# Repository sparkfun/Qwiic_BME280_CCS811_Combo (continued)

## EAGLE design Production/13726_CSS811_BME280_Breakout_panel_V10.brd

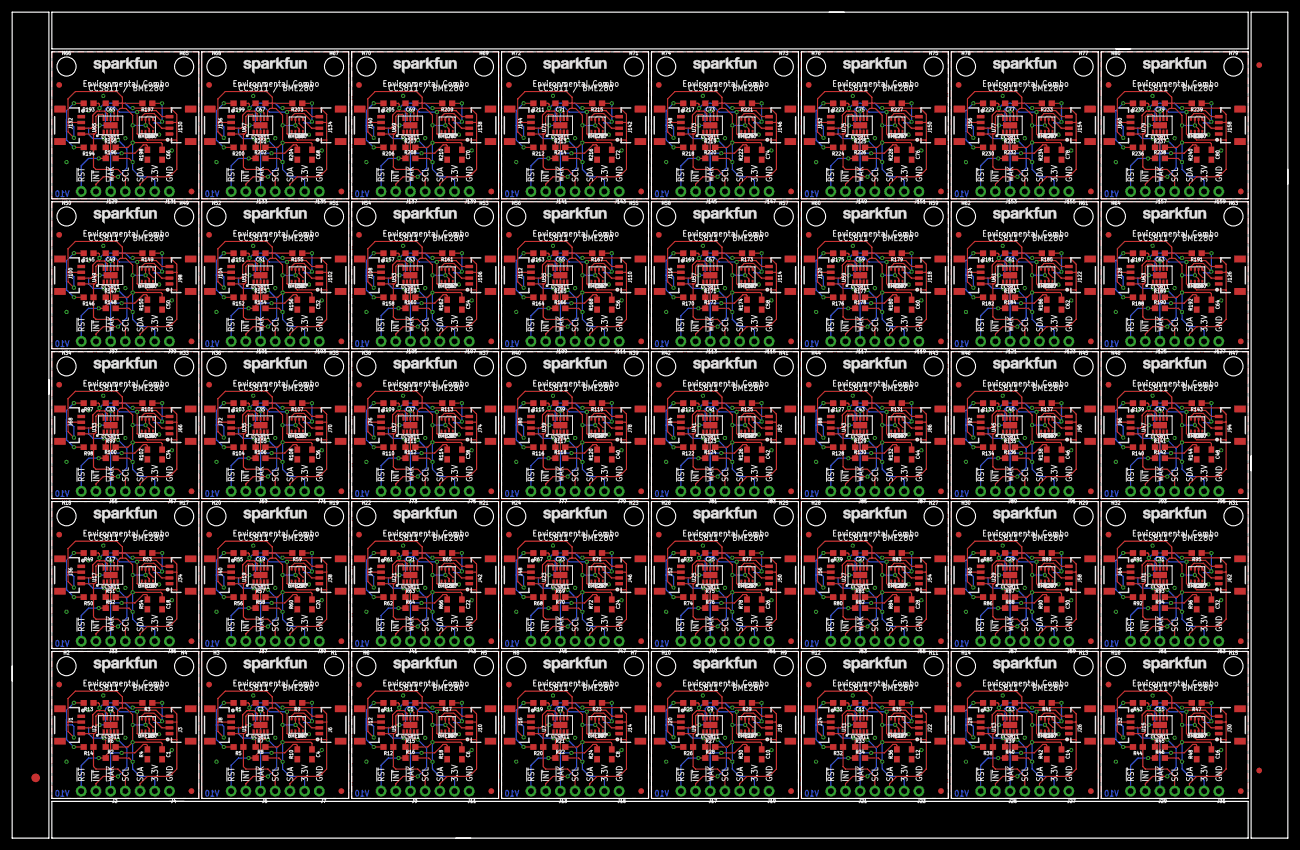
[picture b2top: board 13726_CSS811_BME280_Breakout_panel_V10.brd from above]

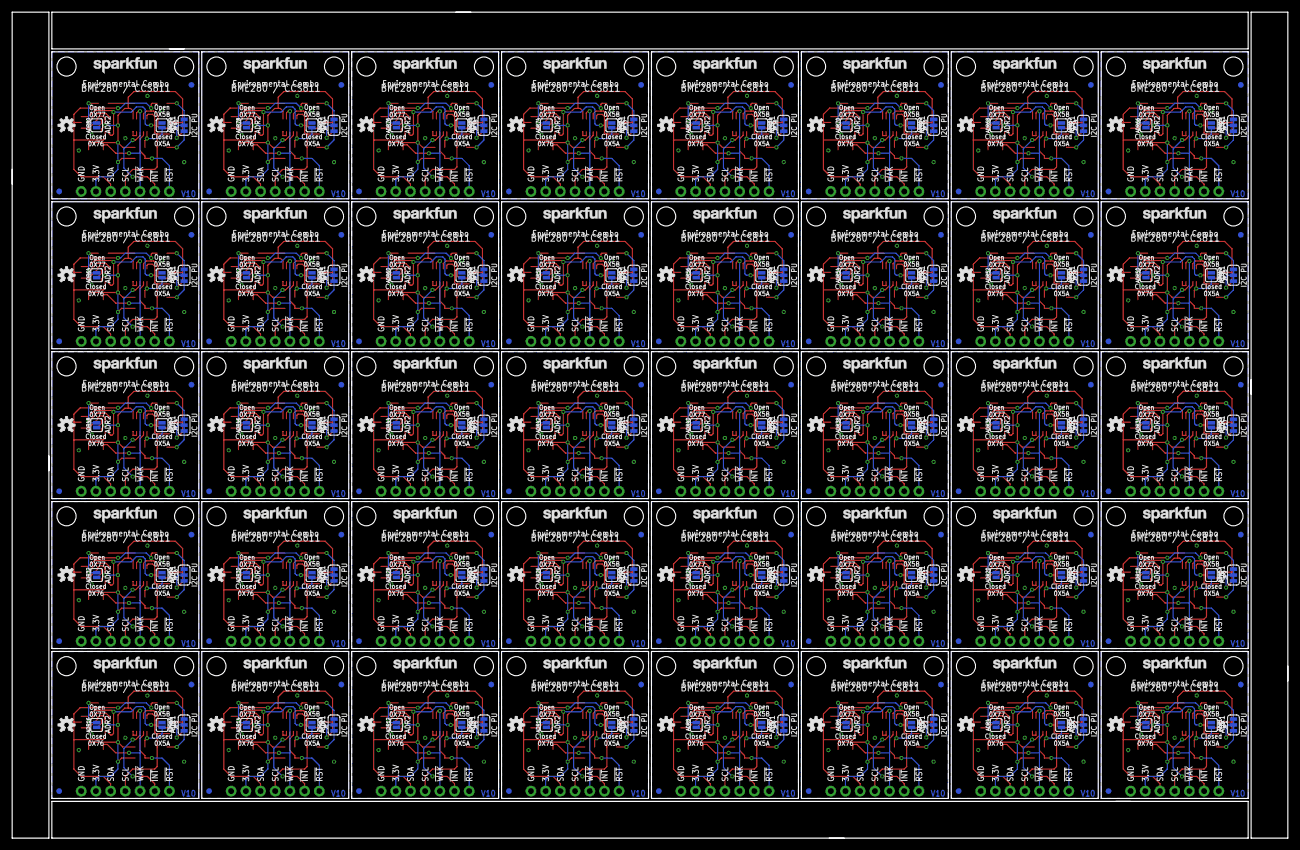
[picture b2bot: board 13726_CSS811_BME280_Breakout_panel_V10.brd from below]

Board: 2 copper layers, 220.5 x 142.7 mm, 1043 parts (280 on the bottom side), 480 nets.

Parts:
ADR1, ADR2, ADR3, ADR4, ADR5, ADR6, ADR7, ADR8, ADR9, ADR10, ADR11, ADR12, ADR13, ADR14, ADR15, ADR16, ADR17, ADR18, ADR19, ADR20, ADR21, ADR22, ADR23, ADR24, ADR25, ADR26, ADR27, ADR28, ADR29, ADR30, ADR31, ADR32, ADR33, ADR34, ADR35, ADR36, ADR37, ADR38, ADR39, ADR40, ADR41, ADR42, ADR43, ADR44, ADR45, ADR46, ADR47, ADR48, ADR49, ADR50, ADR51, ADR52, ADR53, ADR54, ADR55, ADR56, ADR57, ADR58, ADR59, ADR60, ADR61, ADR62, ADR63, ADR64, ADR65, ADR66, ADR67, ADR68, ADR69, ADR70, ADR71, ADR72, ADR73, ADR74, ADR75, ADR76, ADR77, ADR78, ADR79, ADR80: SMT-JUMPER_2_NO_SILK
C1, C4, C6, C8, C10, C12, C14, C16, C18, C20, C22, C24, C26, C28, C30, C32, C34, C36, C38, C40, C42, C44, C46, C48, C50, C52, C54, C56, C58, C60, C62, C64, C66, C68, C70, C72, C74, C76, C78, C80: 0.1uF; 0603
C2, C3, C5, C7, C9, C11, C13, C15, C17, C19, C21, C23, C25, C27, C29, C31, C33, C35, C37, C39, C41, C43, C45, C47, C49, C51, C53, C55, C57, C59, C61, C63, C65, C67, C69, C71, C73, C75, C77, C79: 1.0uF; 0603
E$1: FIDUCIAL-1.5X3
E$7, E$8: FIDUCIAL-1X2
FD1, FD2, FD3, FD4, FD5, FD6, FD7, FD8, FD9, FD10, FD11, FD12, FD13, FD14, FD15, FD16, FD17, FD18, FD19, FD20, FD21, FD22, FD23, FD24, FD25, FD26, FD27, FD28, FD29, FD30, FD31, FD32, FD33, FD34, FD35, FD36, FD37, FD38, FD39, FD40, FD41, FD42, FD43, FD44, FD45, FD46, FD47, FD48, FD49, FD50, FD51, FD52, FD53, FD54, FD55, FD56, FD57, FD58, FD59, FD60, FD61, FD62, FD63, FD64, FD65, FD66, FD67, FD68, FD69, FD70, FD71, FD72, FD73, FD74, FD75, FD76, FD77, FD78, FD79, FD80, FD81, FD82, FD83, FD84, FD85, FD86, FD87, FD88, FD89, FD90, FD91, FD92, FD93, FD94, FD95, FD96, FD97, FD98, FD99, FD100, FD101, FD102, FD103, FD104, FD105, FD106, FD107, FD108, FD109, FD110, FD111, FD112, FD113, FD114, FD115, FD116, FD117, FD118, FD119, FD120, FD121, FD122, FD123, FD124, FD125, FD126, FD127, FD128, FD129, FD130, FD131, FD132, FD133, FD134, FD135, FD136, FD137, FD138, FD139, FD140, FD141, FD142, FD143, FD144, FD145, FD146, FD147, FD148, FD149, FD150, FD151, FD152, FD153, FD154, FD155, FD156, FD157, FD158, FD159, FD160: FIDUCIAL1X2; FIDUCIAL-1X2
H1, H2, H3, H4, H5, H6, H7, H8, H9, H10, H11, H12, H13, H14, H15, H16, H17, H18, H19, H20, H21, H22, H23, H24, H25, H26, H27, H28, H29, H30, H31, H32, H33, H34, H35, H36, H37, H38, H39, H40, H41, H42, H43, H44, H45, H46, H47, H48, H49, H50, H51, H52, H53, H54, H55, H56, H57, H58, H59, H60, H61, H62, H63, H64, H65, H66, H67, H68, H69, H70, H71, H72, H73, H74, H75, H76, H77, H78, H79, H80: STAND-OFF
J1, J3, J6, J8, J10, J12, J14, J16, J18, J20, J22, J24, J26, J28, J30, J32, J34, J36, J38, J40, J42, J44, J46, J48, J50, J52, J54, J56, J58, J60, J62, J64, J66, J68, J70, J72, J74, J76, J78, J80, J82, J84, J86, J88, J90, J92, J94, J96, J98, J100, J102, J104, J106, J108, J110, J112, J114, J116, J118, J120, J122, J124, J126, J128, J130, J132, J134, J136, J138, J140, J142, J144, J146, J148, J150, J152, J154, J156, J158, J160: Qwiic Right Angle; 1X04_1MM_RA
J2, J5, J9, J13, J17, J21, J25, J29, J33, J37, J41, J45, J49, J53, J57, J61, J65, J69, J73, J77, J81, J85, J89, J93, J97, J101, J105, J109, J113, J117, J121, J125, J129, J133, J137, J141, J145, J149, J153, J157: CCS811 Options; 1X03_NO_SILK
J4, J7, J11, J15, J19, J23, J27, J31, J35, J39, J43, J47, J51, J55, J59, J63, J67, J71, J75, J79, J83, J87, J91, J95, J99, J103, J107, J111, J115, J119, J123, J127, J131, J135, J139, J143, J147, J151, J155, J159: PTH; 1X04_NO_SILK
JP1, JP2, JP3, JP4, JP5, JP6, JP7, JP8, JP9, JP10, JP11, JP12, JP13, JP14, JP15, JP16, JP17, JP18, JP19, JP20, JP21, JP22, JP23, JP24, JP25, JP26, JP27, JP28, JP29, JP30, JP31, JP32, JP33, JP34, JP35, JP36, JP37, JP38, JP39, JP40: SMT-JUMPER_3_2-NC_TRACE_SILK
LOGO1, LOGO3, LOGO5, LOGO6, LOGO8, LOGO9, LOGO11, LOGO12, LOGO14, LOGO15, LOGO17, LOGO18, LOGO20, LOGO21, LOGO23, LOGO24, LOGO26, LOGO27, LOGO29, LOGO30, LOGO32, LOGO33, LOGO35, LOGO36, LOGO38, LOGO39, LOGO41, LOGO42, LOGO44, LOGO45, LOGO47, LOGO48, LOGO50, LOGO51, LOGO53, LOGO54, LOGO56, LOGO57, LOGO59, LOGO60, LOGO62, LOGO63, LOGO65, LOGO66, LOGO68, LOGO69, LOGO71, LOGO72, LOGO74, LOGO75, LOGO77, LOGO78, LOGO80, LOGO81, LOGO83, LOGO84, LOGO86, LOGO87, LOGO89, LOGO90, LOGO92, LOGO93, LOGO95, LOGO96, LOGO98, LOGO99, LOGO101, LOGO102, LOGO104, LOGO105, LOGO107, LOGO108, LOGO110, LOGO111, LOGO113, LOGO114, LOGO116, LOGO117, LOGO119, LOGO120: SFE_LOGO_NAME.1_INCH; SFE_LOGO_NAME_.1
LOGO2, LOGO4, LOGO7, LOGO10, LOGO13, LOGO16, LOGO19, LOGO22, LOGO25, LOGO28, LOGO31, LOGO34, LOGO37, LOGO40, LOGO43, LOGO46, LOGO49, LOGO52, LOGO55, LOGO58, LOGO61, LOGO64, LOGO67, LOGO70, LOGO73, LOGO76, LOGO79, LOGO82, LOGO85, LOGO88, LOGO91, LOGO94, LOGO97, LOGO100, LOGO103, LOGO106, LOGO109, LOGO112, LOGO115, LOGO118: OSHW-LOGOS; OSHW-LOGO-S
R1, R2, R5, R8, R11, R12, R13, R14, R16, R19, R20, R22, R25, R26, R28, R31, R32, R34, R37, R38, R40, R43, R44, R46, R49, R50, R52, R55, R56, R58, R61, R62, R64, R67, R68, R70, R73, R74, R76, R79, R80, R82, R85, R86, R88, R91, R92, R94, R97, R98, R100, R103, R104, R106, R109, R110, R112, R115, R116, R118, R121, R122, R124, R127, R128, R130, R133, R134, R136, R139, R140, R142, R145, R146, R148, R151, R152, R154, R157, R158, R160, R163, R164, R166, R169, R170, R172, R175, R176, R178, R181, R182, R184, R187, R188, R190, R193, R194, R196, R199, R200, R202, R205, R206, R208, R211, R212, R214, R217, R218, R220, R223, R224, R226, R229, R230, R232, R235, R236, R238: 4.7k; 0603
R3, R4, R6, R7, R9, R10, R15, R17, R18, R21, R23, R24, R27, R29, R30, R33, R35, R36, R39, R41, R42, R45, R47, R48, R51, R53, R54, R57, R59, R60, R63, R65, R66, R69, R71, R72, R75, R77, R78, R81, R83, R84, R87, R89, R90, R93, R95, R96, R99, R101, R102, R105, R107, R108, R111, R113, R114, R117, R119, R120, R123, R125, R126, R129, R131, R132, R135, R137, R138, R141, R143, R144, R147, R149, R150, R153, R155, R156, R159, R161, R162, R165, R167, R168, R171, R173, R174, R177, R179, R180, R183, R185, R186, R189, R191, R192, R195, R197, R198, R201, R203, R204, R207, R209, R210, R213, R215, R216, R219, R221, R222, R225, R227, R228, R231, R233, R234, R237, R239, R240: 100k; 0603
U1, U2, U5, U7, U9, U11, U13, U15, U17, U19, U21, U23, U25, U27, U29, U31, U33, U35, U37, U39, U41, U43, U45, U47, U49, U51, U53, U55, U57, U59, U61, U63, U65, U67, U69, U71, U73, U75, U77, U79: CCS811; LGA10
U3, U4, U6, U8, U10, U12, U14, U16, U18, U20, U22, U24, U26, U28, U30, U32, U34, U36, U38, U40, U42, U44, U46, U48, U50, U52, U54, U56, U58, U60, U62, U64, U66, U68, U70, U72, U74, U76, U78, U80: BME280; LGA-8-2.5X2.5

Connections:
3.3V: C1.1, C2.1, J1.2, J3.2, J4.2, JP1.2, R2.2, R3.2, R6.2, U2.6, U3.2, U3.6, U3.8
3.3V1: C3.1, C4.1, J6.2, J7.2, J8.2, JP2.2, R7.2, R8.2, R9.2, U1.6, U4.2, U4.6, U4.8
3.3V2: C5.1, C6.1, J10.2, J11.2, J12.2, JP3.2, R15.2, R16.2, R17.2, U5.6, U6.2, U6.6, U6.8
3.3V3: C7.1, C8.1, J14.2, J15.2, J16.2, JP4.2, R21.2, R22.2, R23.2, U7.6, U8.2, U8.6, U8.8
3.3V4: C9.1, C10.1, J18.2, J19.2, J20.2, JP5.2, R27.2, R28.2, R29.2, U9.6, U10.2, U10.6, U10.8
3.3V5: C11.1, C12.1, J22.2, J23.2, J24.2, JP6.2, R33.2, R34.2, R35.2, U11.6, U12.2, U12.6, U12.8
3.3V6: C13.1, C14.1, J26.2, J27.2, J28.2, JP7.2, R39.2, R40.2, R41.2, U13.6, U14.2, U14.6, U14.8
3.3V7: C15.1, C16.1, J30.2, J31.2, J32.2, JP8.2, R45.2, R46.2, R47.2, U15.6, U16.2, U16.6, U16.8
3.3V8: C17.1, C18.1, J34.2, J35.2, J36.2, JP9.2, R51.2, R52.2, R53.2, U17.6, U18.2, U18.6, U18.8
3.3V9: C19.1, C20.1, J38.2, J39.2, J40.2, JP10.2, R57.2, R58.2, R59.2, U19.6, U20.2, U20.6, U20.8
3.3V10: C21.1, C22.1, J42.2, J43.2, J44.2, JP11.2, R63.2, R64.2, R65.2, U21.6, U22.2, U22.6, U22.8
3.3V11: C23.1, C24.1, J46.2, J47.2, J48.2, JP12.2, R69.2, R70.2, R71.2, U23.6, U24.2, U24.6, U24.8
3.3V12: C25.1, C26.1, J50.2, J51.2, J52.2, JP13.2, R75.2, R76.2, R77.2, U25.6, U26.2, U26.6, U26.8
3.3V13: C27.1, C28.1, J54.2, J55.2, J56.2, JP14.2, R81.2, R82.2, R83.2, U27.6, U28.2, U28.6, U28.8
3.3V14: C29.1, C30.1, J58.2, J59.2, J60.2, JP15.2, R87.2, R88.2, R89.2, U29.6, U30.2, U30.6, U30.8
3.3V15: C31.1, C32.1, J62.2, J63.2, J64.2, JP16.2, R93.2, R94.2, R95.2, U31.6, U32.2, U32.6, U32.8
3.3V16: C33.1, C34.1, J66.2, J67.2, J68.2, JP17.2, R99.2, R100.2, R101.2, U33.6, U34.2, U34.6, U34.8
3.3V17: C35.1, C36.1, J70.2, J71.2, J72.2, JP18.2, R105.2, R106.2, R107.2, U35.6, U36.2, U36.6, U36.8
3.3V18: C37.1, C38.1, J74.2, J75.2, J76.2, JP19.2, R111.2, R112.2, R113.2, U37.6, U38.2, U38.6, U38.8
3.3V19: C39.1, C40.1, J78.2, J79.2, J80.2, JP20.2, R117.2, R118.2, R119.2, U39.6, U40.2, U40.6, U40.8
3.3V20: C41.1, C42.1, J82.2, J83.2, J84.2, JP21.2, R123.2, R124.2, R125.2, U41.6, U42.2, U42.6, U42.8
3.3V21: C43.1, C44.1, J86.2, J87.2, J88.2, JP22.2, R129.2, R130.2, R131.2, U43.6, U44.2, U44.6, U44.8
3.3V22: C45.1, C46.1, J90.2, J91.2, J92.2, JP23.2, R135.2, R136.2, R137.2, U45.6, U46.2, U46.6, U46.8
3.3V23: C47.1, C48.1, J94.2, J95.2, J96.2, JP24.2, R141.2, R142.2, R143.2, U47.6, U48.2, U48.6, U48.8
3.3V24: C49.1, C50.1, J98.2, J99.2, J100.2, JP25.2, R147.2, R148.2, R149.2, U49.6, U50.2, U50.6, U50.8
3.3V25: C51.1, C52.1, J102.2, J103.2, J104.2, JP26.2, R153.2, R154.2, R155.2, U51.6, U52.2, U52.6, U52.8
3.3V26: C53.1, C54.1, J106.2, J107.2, J108.2, JP27.2, R159.2, R160.2, R161.2, U53.6, U54.2, U54.6, U54.8
3.3V27: C55.1, C56.1, J110.2, J111.2, J112.2, JP28.2, R165.2, R166.2, R167.2, U55.6, U56.2, U56.6, U56.8
3.3V28: C57.1, C58.1, J114.2, J115.2, J116.2, JP29.2, R171.2, R172.2, R173.2, U57.6, U58.2, U58.6, U58.8
3.3V29: C59.1, C60.1, J118.2, J119.2, J120.2, JP30.2, R177.2, R178.2, R179.2, U59.6, U60.2, U60.6, U60.8
3.3V30: C61.1, C62.1, J122.2, J123.2, J124.2, JP31.2, R183.2, R184.2, R185.2, U61.6, U62.2, U62.6, U62.8
3.3V31: C63.1, C64.1, J126.2, J127.2, J128.2, JP32.2, R189.2, R190.2, R191.2, U63.6, U64.2, U64.6, U64.8
3.3V32: C65.1, C66.1, J130.2, J131.2, J132.2, JP33.2, R195.2, R196.2, R197.2, U65.6, U66.2, U66.6, U66.8
3.3V33: C67.1, C68.1, J134.2, J135.2, J136.2, JP34.2, R201.2, R202.2, R203.2, U67.6, U68.2, U68.6, U68.8
3.3V34: C69.1, C70.1, J138.2, J139.2, J140.2, JP35.2, R207.2, R208.2, R209.2, U69.6, U70.2, U70.6, U70.8
3.3V35: C71.1, C72.1, J142.2, J143.2, J144.2, JP36.2, R213.2, R214.2, R215.2, U71.6, U72.2, U72.6, U72.8
3.3V36: C73.1, C74.1, J146.2, J147.2, J148.2, JP37.2, R219.2, R220.2, R221.2, U73.6, U74.2, U74.6, U74.8
3.3V37: C75.1, C76.1, J150.2, J151.2, J152.2, JP38.2, R225.2, R226.2, R227.2, U75.6, U76.2, U76.6, U76.8
3.3V38: C77.1, C78.1, J154.2, J155.2, J156.2, JP39.2, R231.2, R232.2, R233.2, U77.6, U78.2, U78.6, U78.8
3.3V39: C79.1, C80.1, J158.2, J159.2, J160.2, JP40.2, R237.2, R238.2, R239.2, U79.6, U80.2, U80.6, U80.8
!INT: J2.2, U2.3
!INT1: J5.2, U1.3
!INT2: J9.2, U5.3
!INT3: J13.2, U7.3
!INT4: J17.2, U9.3
!INT5: J21.2, U11.3
!INT6: J25.2, U13.3
!INT7: J29.2, U15.3
!INT8: J33.2, U17.3
!INT9: J37.2, U19.3
!INT10: J41.2, U21.3
!INT11: J45.2, U23.3
!INT12: J49.2, U25.3
!INT13: J53.2, U27.3
!INT14: J57.2, U29.3
!INT15: J61.2, U31.3
!INT16: J65.2, U33.3
!INT17: J69.2, U35.3
!INT18: J73.2, U37.3
!INT19: J77.2, U39.3
!INT20: J81.2, U41.3
!INT21: J85.2, U43.3
!INT22: J89.2, U45.3
!INT23: J93.2, U47.3
!INT24: J97.2, U49.3
!INT25: J101.2, U51.3
!INT26: J105.2, U53.3
!INT27: J109.2, U55.3
!INT28: J113.2, U57.3
!INT29: J117.2, U59.3
!INT30: J121.2, U61.3
!INT31: J125.2, U63.3
!INT32: J129.2, U65.3
!INT33: J133.2, U67.3
!INT34: J137.2, U69.3
!INT35: J141.2, U71.3
!INT36: J145.2, U73.3
!INT37: J149.2, U75.3
!INT38: J153.2, U77.3
!INT39: J157.2, U79.3
!RST: J2.3, R2.1, U2.2
!RST1: J5.3, R8.1, U1.2
!RST2: J9.3, R16.1, U5.2
!RST3: J13.3, R22.1, U7.2
!RST4: J17.3, R28.1, U9.2
!RST5: J21.3, R34.1, U11.2
!RST6: J25.3, R40.1, U13.2
!RST7: J29.3, R46.1, U15.2
!RST8: J33.3, R52.1, U17.2
!RST9: J37.3, R58.1, U19.2
!RST10: J41.3, R64.1, U21.2
!RST11: J45.3, R70.1, U23.2
!RST12: J49.3, R76.1, U25.2
!RST13: J53.3, R82.1, U27.2
!RST14: J57.3, R88.1, U29.2
!RST15: J61.3, R94.1, U31.2
!RST16: J65.3, R100.1, U33.2
!RST17: J69.3, R106.1, U35.2
!RST18: J73.3, R112.1, U37.2
!RST19: J77.3, R118.1, U39.2
!RST20: J81.3, R124.1, U41.2
!RST21: J85.3, R130.1, U43.2
!RST22: J89.3, R136.1, U45.2
!RST23: J93.3, R142.1, U47.2
!RST24: J97.3, R148.1, U49.2
!RST25: J101.3, R154.1, U51.2
!RST26: J105.3, R160.1, U53.2
!RST27: J109.3, R166.1, U55.2
!RST28: J113.3, R172.1, U57.2
!RST29: J117.3, R178.1, U59.2
!RST30: J121.3, R184.1, U61.2
!RST31: J125.3, R190.1, U63.2
!RST32: J129.3, R196.1, U65.2
!RST33: J133.3, R202.1, U67.2
!RST34: J137.3, R208.1, U69.2
!RST35: J141.3, R214.1, U71.2
!RST36: J145.3, R220.1, U73.2
!RST37: J149.3, R226.1, U75.2
!RST38: J153.3, R232.1, U77.2
!RST39: J157.3, R238.1, U79.2
!WAKE: J2.1, R4.2, U2.7
!WAKE1: J5.1, R10.2, U1.7
!WAKE2: J9.1, R18.2, U5.7
!WAKE3: J13.1, R24.2, U7.7
!WAKE4: J17.1, R30.2, U9.7
!WAKE5: J21.1, R36.2, U11.7
!WAKE6: J25.1, R42.2, U13.7
!WAKE7: J29.1, R48.2, U15.7
!WAKE8: J33.1, R54.2, U17.7
!WAKE9: J37.1, R60.2, U19.7
!WAKE10: J41.1, R66.2, U21.7
!WAKE11: J45.1, R72.2, U23.7
!WAKE12: J49.1, R78.2, U25.7
!WAKE13: J53.1, R84.2, U27.7
!WAKE14: J57.1, R90.2, U29.7
!WAKE15: J61.1, R96.2, U31.7
!WAKE16: J65.1, R102.2, U33.7
!WAKE17: J69.1, R108.2, U35.7
!WAKE18: J73.1, R114.2, U37.7
!WAKE19: J77.1, R120.2, U39.7
!WAKE20: J81.1, R126.2, U41.7
!WAKE21: J85.1, R132.2, U43.7
!WAKE22: J89.1, R138.2, U45.7
!WAKE23: J93.1, R144.2, U47.7
!WAKE24: J97.1, R150.2, U49.7
!WAKE25: J101.1, R156.2, U51.7
!WAKE26: J105.1, R162.2, U53.7
!WAKE27: J109.1, R168.2, U55.7
!WAKE28: J113.1, R174.2, U57.7
!WAKE29: J117.1, R180.2, U59.7
!WAKE30: J121.1, R186.2, U61.7
!WAKE31: J125.1, R192.2, U63.7
!WAKE32: J129.1, R198.2, U65.7
!WAKE33: J133.1, R204.2, U67.7
!WAKE34: J137.1, R210.2, U69.7
!WAKE35: J141.1, R216.2, U71.7
!WAKE36: J145.1, R222.2, U73.7
!WAKE37: J149.1, R228.2, U75.7
!WAKE38: J153.1, R234.2, U77.7
!WAKE39: J157.1, R240.2, U79.7
CCS811_ADDR: ADR1.2, R6.1, U2.1
CCS811_ADDR1: ADR3.2, R7.1, U1.1
CCS811_ADDR2: ADR5.2, R15.1, U5.1
CCS811_ADDR3: ADR7.2, R21.1, U7.1
CCS811_ADDR4: ADR9.2, R27.1, U9.1
CCS811_ADDR5: ADR11.2, R33.1, U11.1
CCS811_ADDR6: ADR13.2, R39.1, U13.1
CCS811_ADDR7: ADR15.2, R45.1, U15.1
CCS811_ADDR8: ADR17.2, R51.1, U17.1
CCS811_ADDR9: ADR19.2, R57.1, U19.1
CCS811_ADDR10: ADR21.2, R63.1, U21.1
CCS811_ADDR11: ADR23.2, R69.1, U23.1
CCS811_ADDR12: ADR25.2, R75.1, U25.1
CCS811_ADDR13: ADR27.2, R81.1, U27.1
CCS811_ADDR14: ADR29.2, R87.1, U29.1
CCS811_ADDR15: ADR31.2, R93.1, U31.1
CCS811_ADDR16: ADR33.2, R99.1, U33.1
CCS811_ADDR17: ADR35.2, R105.1, U35.1
CCS811_ADDR18: ADR37.2, R111.1, U37.1
CCS811_ADDR19: ADR39.2, R117.1, U39.1
CCS811_ADDR20: ADR41.2, R123.1, U41.1
CCS811_ADDR21: ADR43.2, R129.1, U43.1
CCS811_ADDR22: ADR45.2, R135.1, U45.1
CCS811_ADDR23: ADR47.2, R141.1, U47.1
CCS811_ADDR24: ADR49.2, R147.1, U49.1
CCS811_ADDR25: ADR51.2, R153.1, U51.1
CCS811_ADDR26: ADR53.2, R159.1, U53.1
CCS811_ADDR27: ADR55.2, R165.1, U55.1
CCS811_ADDR28: ADR57.2, R171.1, U57.1
CCS811_ADDR29: ADR59.2, R177.1, U59.1
CCS811_ADDR30: ADR61.2, R183.1, U61.1
CCS811_ADDR31: ADR63.2, R189.1, U63.1
CCS811_ADDR32: ADR65.2, R195.1, U65.1
CCS811_ADDR33: ADR67.2, R201.1, U67.1
CCS811_ADDR34: ADR69.2, R207.1, U69.1
CCS811_ADDR35: ADR71.2, R213.1, U71.1
CCS811_ADDR36: ADR73.2, R219.1, U73.1
CCS811_ADDR37: ADR75.2, R225.1, U75.1
CCS811_ADDR38: ADR77.2, R231.1, U77.1
CCS811_ADDR39: ADR79.2, R237.1, U79.1
GND: ADR1.1, ADR2.1, C1.2, C2.2, J1.1, J3.1, J4.1, R4.1, U2.EP, U3.1, U3.7
GND1: ADR3.1, ADR4.1, C3.2, C4.2, J6.1, J7.1, J8.1, R10.1, U1.EP, U4.1, U4.7
GND2: ADR5.1, ADR6.1, C5.2, C6.2, J10.1, J11.1, J12.1, R18.1, U5.EP, U6.1, U6.7
GND3: ADR7.1, ADR8.1, C7.2, C8.2, J14.1, J15.1, J16.1, R24.1, U7.EP, U8.1, U8.7
GND4: ADR9.1, ADR10.1, C9.2, C10.2, J18.1, J19.1, J20.1, R30.1, U9.EP, U10.1, U10.7
GND5: ADR11.1, ADR12.1, C11.2, C12.2, J22.1, J23.1, J24.1, R36.1, U11.EP, U12.1, U12.7
GND6: ADR13.1, ADR14.1, C13.2, C14.2, J26.1, J27.1, J28.1, R42.1, U13.EP, U14.1, U14.7
GND7: ADR15.1, ADR16.1, C15.2, C16.2, J30.1, J31.1, J32.1, R48.1, U15.EP, U16.1, U16.7
GND8: ADR17.1, ADR18.1, C17.2, C18.2, J34.1, J35.1, J36.1, R54.1, U17.EP, U18.1, U18.7
GND9: ADR19.1, ADR20.1, C19.2, C20.2, J38.1, J39.1, J40.1, R60.1, U19.EP, U20.1, U20.7
GND10: ADR21.1, ADR22.1, C21.2, C22.2, J42.1, J43.1, J44.1, R66.1, U21.EP, U22.1, U22.7
GND11: ADR23.1, ADR24.1, C23.2, C24.2, J46.1, J47.1, J48.1, R72.1, U23.EP, U24.1, U24.7
GND12: ADR25.1, ADR26.1, C25.2, C26.2, J50.1, J51.1, J52.1, R78.1, U25.EP, U26.1, U26.7
GND13: ADR27.1, ADR28.1, C27.2, C28.2, J54.1, J55.1, J56.1, R84.1, U27.EP, U28.1, U28.7
GND14: ADR29.1, ADR30.1, C29.2, C30.2, J58.1, J59.1, J60.1, R90.1, U29.EP, U30.1, U30.7
GND15: ADR31.1, ADR32.1, C31.2, C32.2, J62.1, J63.1, J64.1, R96.1, U31.EP, U32.1, U32.7
GND16: ADR33.1, ADR34.1, C33.2, C34.2, J66.1, J67.1, J68.1, R102.1, U33.EP, U34.1, U34.7
GND17: ADR35.1, ADR36.1, C35.2, C36.2, J70.1, J71.1, J72.1, R108.1, U35.EP, U36.1, U36.7
GND18: ADR37.1, ADR38.1, C37.2, C38.2, J74.1, J75.1, J76.1, R114.1, U37.EP, U38.1, U38.7
GND19: ADR39.1, ADR40.1, C39.2, C40.2, J78.1, J79.1, J80.1, R120.1, U39.EP, U40.1, U40.7
GND20: ADR41.1, ADR42.1, C41.2, C42.2, J82.1, J83.1, J84.1, R126.1, U41.EP, U42.1, U42.7
GND21: ADR43.1, ADR44.1, C43.2, C44.2, J86.1, J87.1, J88.1, R132.1, U43.EP, U44.1, U44.7
GND22: ADR45.1, ADR46.1, C45.2, C46.2, J90.1, J91.1, J92.1, R138.1, U45.EP, U46.1, U46.7
GND23: ADR47.1, ADR48.1, C47.2, C48.2, J94.1, J95.1, J96.1, R144.1, U47.EP, U48.1, U48.7
GND24: ADR49.1, ADR50.1, C49.2, C50.2, J98.1, J99.1, J100.1, R150.1, U49.EP, U50.1, U50.7
GND25: ADR51.1, ADR52.1, C51.2, C52.2, J102.1, J103.1, J104.1, R156.1, U51.EP, U52.1, U52.7
GND26: ADR53.1, ADR54.1, C53.2, C54.2, J106.1, J107.1, J108.1, R162.1, U53.EP, U54.1, U54.7
GND27: ADR55.1, ADR56.1, C55.2, C56.2, J110.1, J111.1, J112.1, R168.1, U55.EP, U56.1, U56.7
GND28: ADR57.1, ADR58.1, C57.2, C58.2, J114.1, J115.1, J116.1, R174.1, U57.EP, U58.1, U58.7
GND29: ADR59.1, ADR60.1, C59.2, C60.2, J118.1, J119.1, J120.1, R180.1, U59.EP, U60.1, U60.7
GND30: ADR61.1, ADR62.1, C61.2, C62.2, J122.1, J123.1, J124.1, R186.1, U61.EP, U62.1, U62.7
GND31: ADR63.1, ADR64.1, C63.2, C64.2, J126.1, J127.1, J128.1, R192.1, U63.EP, U64.1, U64.7
GND32: ADR65.1, ADR66.1, C65.2, C66.2, J130.1, J131.1, J132.1, R198.1, U65.EP, U66.1, U66.7
GND33: ADR67.1, ADR68.1, C67.2, C68.2, J134.1, J135.1, J136.1, R204.1, U67.EP, U68.1, U68.7
GND34: ADR69.1, ADR70.1, C69.2, C70.2, J138.1, J139.1, J140.1, R210.1, U69.EP, U70.1, U70.7
GND35: ADR71.1, ADR72.1, C71.2, C72.2, J142.1, J143.1, J144.1, R216.1, U71.EP, U72.1, U72.7
GND36: ADR73.1, ADR74.1, C73.2, C74.2, J146.1, J147.1, J148.1, R222.1, U73.EP, U74.1, U74.7
GND37: ADR75.1, ADR76.1, C75.2, C76.2, J150.1, J151.1, J152.1, R228.1, U75.EP, U76.1, U76.7
GND38: ADR77.1, ADR78.1, C77.2, C78.2, J154.1, J155.1, J156.1, R234.1, U77.EP, U78.1, U78.7
GND39: ADR79.1, ADR80.1, C79.2, C80.2, J158.1, J159.1, J160.1, R240.1, U79.EP, U80.1, U80.7
unnamed: JP2.3, R1.2
unnamed: JP2.1, R5.2
unnamed: JP1.3, R13.2
unnamed: JP1.1, R14.2
unnamed: JP3.3, R11.2
unnamed: JP3.1, R12.2
unnamed: JP4.3, R19.2
unnamed: JP4.1, R20.2
unnamed: JP5.3, R25.2
unnamed: JP5.1, R26.2
unnamed: JP6.3, R31.2
unnamed: JP6.1, R32.2
unnamed: JP7.3, R37.2
unnamed: JP7.1, R38.2
unnamed: JP8.3, R43.2
unnamed: JP8.1, R44.2
unnamed: JP9.3, R49.2
unnamed: JP9.1, R50.2
unnamed: JP10.3, R55.2
unnamed: JP10.1, R56.2
unnamed: JP11.3, R61.2
unnamed: JP11.1, R62.2
unnamed: JP12.3, R67.2
unnamed: JP12.1, R68.2
unnamed: JP13.3, R73.2
unnamed: JP13.1, R74.2
unnamed: JP14.3, R79.2
unnamed: JP14.1, R80.2
unnamed: JP15.3, R85.2
unnamed: JP15.1, R86.2
unnamed: JP16.3, R91.2
unnamed: JP16.1, R92.2
unnamed: JP17.3, R97.2
unnamed: JP17.1, R98.2
unnamed: JP18.3, R103.2
unnamed: JP18.1, R104.2
unnamed: JP19.3, R109.2
unnamed: JP19.1, R110.2
unnamed: JP20.3, R115.2
unnamed: JP20.1, R116.2
unnamed: JP21.3, R121.2
unnamed: JP21.1, R122.2
unnamed: JP22.3, R127.2
unnamed: JP22.1, R128.2
unnamed: JP23.3, R133.2
unnamed: JP23.1, R134.2
unnamed: JP24.3, R139.2
unnamed: JP24.1, R140.2
unnamed: JP25.3, R145.2
unnamed: JP25.1, R146.2
unnamed: JP26.3, R151.2
unnamed: JP26.1, R152.2
unnamed: JP27.3, R157.2
unnamed: JP27.1, R158.2
unnamed: JP28.3, R163.2
unnamed: JP28.1, R164.2
unnamed: JP29.3, R169.2
unnamed: JP29.1, R170.2
unnamed: JP30.3, R175.2
unnamed: JP30.1, R176.2
unnamed: JP31.3, R181.2
unnamed: JP31.1, R182.2
unnamed: JP32.3, R187.2
unnamed: JP32.1, R188.2
unnamed: JP33.3, R193.2
unnamed: JP33.1, R194.2
unnamed: JP34.3, R199.2
unnamed: JP34.1, R200.2
unnamed: JP35.3, R205.2
unnamed: JP35.1, R206.2
unnamed: JP36.3, R211.2
unnamed: JP36.1, R212.2
unnamed: JP37.3, R217.2
unnamed: JP37.1, R218.2
unnamed: JP38.3, R223.2
unnamed: JP38.1, R224.2
unnamed: JP39.3, R229.2
unnamed: JP39.1, R230.2
unnamed: JP40.3, R235.2
unnamed: JP40.1, R236.2
NTC_SENSE: U2.4, U2.5
NTC_SENSE1: U1.4, U1.5
NTC_SENSE2: U5.4, U5.5
NTC_SENSE3: U7.4, U7.5
NTC_SENSE4: U9.4, U9.5
NTC_SENSE5: U11.4, U11.5
NTC_SENSE6: U13.4, U13.5
NTC_SENSE7: U15.4, U15.5
NTC_SENSE8: U17.4, U17.5
NTC_SENSE9: U19.4, U19.5
NTC_SENSE10: U21.4, U21.5
NTC_SENSE11: U23.4, U23.5
NTC_SENSE12: U25.4, U25.5
NTC_SENSE13: U27.4, U27.5
NTC_SENSE14: U29.4, U29.5
NTC_SENSE15: U31.4, U31.5
NTC_SENSE16: U33.4, U33.5
NTC_SENSE17: U35.4, U35.5
NTC_SENSE18: U37.4, U37.5
NTC_SENSE19: U39.4, U39.5
NTC_SENSE20: U41.4, U41.5
NTC_SENSE21: U43.4, U43.5
NTC_SENSE22: U45.4, U45.5
NTC_SENSE23: U47.4, U47.5
NTC_SENSE24: U49.4, U49.5
NTC_SENSE25: U51.4, U51.5
NTC_SENSE26: U53.4, U53.5
NTC_SENSE27: U55.4, U55.5
NTC_SENSE28: U57.4, U57.5
NTC_SENSE29: U59.4, U59.5
NTC_SENSE30: U61.4, U61.5
NTC_SENSE31: U63.4, U63.5
NTC_SENSE32: U65.4, U65.5
NTC_SENSE33: U67.4, U67.5
NTC_SENSE34: U69.4, U69.5
NTC_SENSE35: U71.4, U71.5
NTC_SENSE36: U73.4, U73.5
NTC_SENSE37: U75.4, U75.5
NTC_SENSE38: U77.4, U77.5
NTC_SENSE39: U79.4, U79.5
SCL: J1.4, J3.4, J4.4, R14.1, U2.10, U3.4
SCL1: J6.4, J7.4, J8.4, R5.1, U1.10, U4.4
SCL2: J10.4, J11.4, J12.4, R12.1, U5.10, U6.4
SCL3: J14.4, J15.4, J16.4, R20.1, U7.10, U8.4
SCL4: J18.4, J19.4, J20.4, R26.1, U9.10, U10.4
SCL5: J22.4, J23.4, J24.4, R32.1, U11.10, U12.4
SCL6: J26.4, J27.4, J28.4, R38.1, U13.10, U14.4
SCL7: J30.4, J31.4, J32.4, R44.1, U15.10, U16.4
SCL8: J34.4, J35.4, J36.4, R50.1, U17.10, U18.4
SCL9: J38.4, J39.4, J40.4, R56.1, U19.10, U20.4
SCL10: J42.4, J43.4, J44.4, R62.1, U21.10, U22.4
SCL11: J46.4, J47.4, J48.4, R68.1, U23.10, U24.4
SCL12: J50.4, J51.4, J52.4, R74.1, U25.10, U26.4
SCL13: J54.4, J55.4, J56.4, R80.1, U27.10, U28.4
SCL14: J58.4, J59.4, J60.4, R86.1, U29.10, U30.4
SCL15: J62.4, J63.4, J64.4, R92.1, U31.10, U32.4
SCL16: J66.4, J67.4, J68.4, R98.1, U33.10, U34.4
SCL17: J70.4, J71.4, J72.4, R104.1, U35.10, U36.4
SCL18: J74.4, J75.4, J76.4, R110.1, U37.10, U38.4
SCL19: J78.4, J79.4, J80.4, R116.1, U39.10, U40.4
SCL20: J82.4, J83.4, J84.4, R122.1, U41.10, U42.4
SCL21: J86.4, J87.4, J88.4, R128.1, U43.10, U44.4
SCL22: J90.4, J91.4, J92.4, R134.1, U45.10, U46.4
SCL23: J94.4, J95.4, J96.4, R140.1, U47.10, U48.4
SCL24: J98.4, J99.4, J100.4, R146.1, U49.10, U50.4
SCL25: J102.4, J103.4, J104.4, R152.1, U51.10, U52.4
SCL26: J106.4, J107.4, J108.4, R158.1, U53.10, U54.4
SCL27: J110.4, J111.4, J112.4, R164.1, U55.10, U56.4
SCL28: J114.4, J115.4, J116.4, R170.1, U57.10, U58.4
SCL29: J118.4, J119.4, J120.4, R176.1, U59.10, U60.4
SCL30: J122.4, J123.4, J124.4, R182.1, U61.10, U62.4
SCL31: J126.4, J127.4, J128.4, R188.1, U63.10, U64.4
SCL32: J130.4, J131.4, J132.4, R194.1, U65.10, U66.4
SCL33: J134.4, J135.4, J136.4, R200.1, U67.10, U68.4
SCL34: J138.4, J139.4, J140.4, R206.1, U69.10, U70.4
SCL35: J142.4, J143.4, J144.4, R212.1, U71.10, U72.4
SCL36: J146.4, J147.4, J148.4, R218.1, U73.10, U74.4
SCL37: J150.4, J151.4, J152.4, R224.1, U75.10, U76.4
SCL38: J154.4, J155.4, J156.4, R230.1, U77.10, U78.4
SCL39: J158.4, J159.4, J160.4, R236.1, U79.10, U80.4
SDA: J1.3, J3.3, J4.3, R13.1, U2.9, U3.3
SDA1: J6.3, J7.3, J8.3, R1.1, U1.9, U4.3
SDA2: J10.3, J11.3, J12.3, R11.1, U5.9, U6.3
SDA3: J14.3, J15.3, J16.3, R19.1, U7.9, U8.3
SDA4: J18.3, J19.3, J20.3, R25.1, U9.9, U10.3
SDA5: J22.3, J23.3, J24.3, R31.1, U11.9, U12.3
SDA6: J26.3, J27.3, J28.3, R37.1, U13.9, U14.3
SDA7: J30.3, J31.3, J32.3, R43.1, U15.9, U16.3
SDA8: J34.3, J35.3, J36.3, R49.1, U17.9, U18.3
SDA9: J38.3, J39.3, J40.3, R55.1, U19.9, U20.3
SDA10: J42.3, J43.3, J44.3, R61.1, U21.9, U22.3
SDA11: J46.3, J47.3, J48.3, R67.1, U23.9, U24.3
SDA12: J50.3, J51.3, J52.3, R73.1, U25.9, U26.3
SDA13: J54.3, J55.3, J56.3, R79.1, U27.9, U28.3
SDA14: J58.3, J59.3, J60.3, R85.1, U29.9, U30.3
SDA15: J62.3, J63.3, J64.3, R91.1, U31.9, U32.3
SDA16: J66.3, J67.3, J68.3, R97.1, U33.9, U34.3
SDA17: J70.3, J71.3, J72.3, R103.1, U35.9, U36.3
SDA18: J74.3, J75.3, J76.3, R109.1, U37.9, U38.3
SDA19: J78.3, J79.3, J80.3, R115.1, U39.9, U40.3
SDA20: J82.3, J83.3, J84.3, R121.1, U41.9, U42.3
SDA21: J86.3, J87.3, J88.3, R127.1, U43.9, U44.3
SDA22: J90.3, J91.3, J92.3, R133.1, U45.9, U46.3
SDA23: J94.3, J95.3, J96.3, R139.1, U47.9, U48.3
SDA24: J98.3, J99.3, J100.3, R145.1, U49.9, U50.3
SDA25: J102.3, J103.3, J104.3, R151.1, U51.9, U52.3
SDA26: J106.3, J107.3, J108.3, R157.1, U53.9, U54.3
SDA27: J110.3, J111.3, J112.3, R163.1, U55.9, U56.3
SDA28: J114.3, J115.3, J116.3, R169.1, U57.9, U58.3
SDA29: J118.3, J119.3, J120.3, R175.1, U59.9, U60.3
SDA30: J122.3, J123.3, J124.3, R181.1, U61.9, U62.3
SDA31: J126.3, J127.3, J128.3, R187.1, U63.9, U64.3
SDA32: J130.3, J131.3, J132.3, R193.1, U65.9, U66.3
SDA33: J134.3, J135.3, J136.3, R199.1, U67.9, U68.3
SDA34: J138.3, J139.3, J140.3, R205.1, U69.9, U70.3
SDA35: J142.3, J143.3, J144.3, R211.1, U71.9, U72.3
SDA36: J146.3, J147.3, J148.3, R217.1, U73.9, U74.3
SDA37: J150.3, J151.3, J152.3, R223.1, U75.9, U76.3
SDA38: J154.3, J155.3, J156.3, R229.1, U77.9, U78.3
SDA39: J158.3, J159.3, J160.3, R235.1, U79.9, U80.3
SDO/ADR: ADR2.2, R3.1, U3.5
SDO/ADR1: ADR4.2, R9.1, U4.5
SDO/ADR2: ADR6.2, R17.1, U6.5
SDO/ADR3: ADR8.2, R23.1, U8.5
SDO/ADR4: ADR10.2, R29.1, U10.5
SDO/ADR5: ADR12.2, R35.1, U12.5
SDO/ADR6: ADR14.2, R41.1, U14.5
SDO/ADR7: ADR16.2, R47.1, U16.5
SDO/ADR8: ADR18.2, R53.1, U18.5
SDO/ADR9: ADR20.2, R59.1, U20.5
SDO/ADR10: ADR22.2, R65.1, U22.5
SDO/ADR11: ADR24.2, R71.1, U24.5
SDO/ADR12: ADR26.2, R77.1, U26.5
SDO/ADR13: ADR28.2, R83.1, U28.5
SDO/ADR14: ADR30.2, R89.1, U30.5
SDO/ADR15: ADR32.2, R95.1, U32.5
SDO/ADR16: ADR34.2, R101.1, U34.5
SDO/ADR17: ADR36.2, R107.1, U36.5
SDO/ADR18: ADR38.2, R113.1, U38.5
SDO/ADR19: ADR40.2, R119.1, U40.5
SDO/ADR20: ADR42.2, R125.1, U42.5
SDO/ADR21: ADR44.2, R131.1, U44.5
SDO/ADR22: ADR46.2, R137.1, U46.5
SDO/ADR23: ADR48.2, R143.1, U48.5
SDO/ADR24: ADR50.2, R149.1, U50.5
SDO/ADR25: ADR52.2, R155.1, U52.5
SDO/ADR26: ADR54.2, R161.1, U54.5
SDO/ADR27: ADR56.2, R167.1, U56.5
SDO/ADR28: ADR58.2, R173.1, U58.5
SDO/ADR29: ADR60.2, R179.1, U60.5
SDO/ADR30: ADR62.2, R185.1, U62.5
SDO/ADR31: ADR64.2, R191.1, U64.5
SDO/ADR32: ADR66.2, R197.1, U66.5
SDO/ADR33: ADR68.2, R203.1, U68.5
SDO/ADR34: ADR70.2, R209.1, U70.5
SDO/ADR35: ADR72.2, R215.1, U72.5
SDO/ADR36: ADR74.2, R221.1, U74.5
SDO/ADR37: ADR76.2, R227.1, U76.5
SDO/ADR38: ADR78.2, R233.1, U78.5
SDO/ADR39: ADR80.2, R239.1, U80.5

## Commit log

2017-06-16 added eagle files
2017-06-19 Added .gitignore, README, etc...
2017-06-20 Updated file structure to match SFE repo
2017-06-20 Updated parts to fit with SFE library
2017-07-05 Pre design review changes
2017-07-05 Added Dimensions
2017-07-06 Added fiducials to bottom of board
2017-07-06 Post design review aesthetic changes
2017-07-07 updated silk for Reds
2017-07-18 added units
2017-07-18 panel
2017-07-25 Changed V to v
2017-08-23 moved engineering checklist
2017-09-06 Actually updated readme
2017-09-06 readme looks good
2017-09-06 readme really looks good
2017-09-06 Added example code
2017-09-07 Added examples
2017-09-07 Squashed 'Libraries/Arduino/' content from commit d0663f3
    git-subtree-dir: Libraries/Arduino
    git-subtree-split: d0663f31b8e9cb3536c5eda6ba2fe3e3023c2f0a
2017-09-07 Added Libraries, cleaned repo
2017-09-07 still fixing library
2017-09-07 Squashed 'Libraries/Arduino/' content from commit 9a2a24d
    git-subtree-dir: Libraries/Arduino
    git-subtree-split: 9a2a24d2b25db1f430d7b6b9ff62c388d72c60e1
2017-09-07 Actually got libraries working
2017-09-08 Fixed readme
2018-10-12 Removing old libs from repo.
